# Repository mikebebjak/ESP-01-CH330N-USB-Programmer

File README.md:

# ESP-01-CH330N-USB-Programmer

This is a very simple but effective USB programmer for the ESP8266-01 Wifi microcontroller.
It uses a new CH330N SOIC-8 chip which is very easy to implement in ESP projects at a very low cost with few additional components.
The repository includes datasheet, drivers, schematics, Eagle board files and gerbers as well as an Eagle library file for the CH330N.
The drivers used for the CH330N are the same as the CH341.<br>

You can purchase the CH330N at: https://lcsc.com/product-detail/USB_CH330N_C108996.html<br>

You will need:<br>

1x CH330N USB transceiver<br>
1x AMS1117 TO-223 3.3V regulator<br>
1x Molex USB-A through-hole connector<br>
1x 8-pin 2mm socket for the ESP<br>
4x 10K 1206 resistors (for pullups and pulldowns)<br>
2x 0.1uF 1206 capacitors<br>
1x 6mm through-hole momentary push button for the reset button<br>
1x large electrolytic capacitor (220uF or higher at 6.3V min.)<br><br>
GPIO 0 is tied to GND permanently so this programmer cannot be used to boot the ESP (though it may sometimes work anyway).

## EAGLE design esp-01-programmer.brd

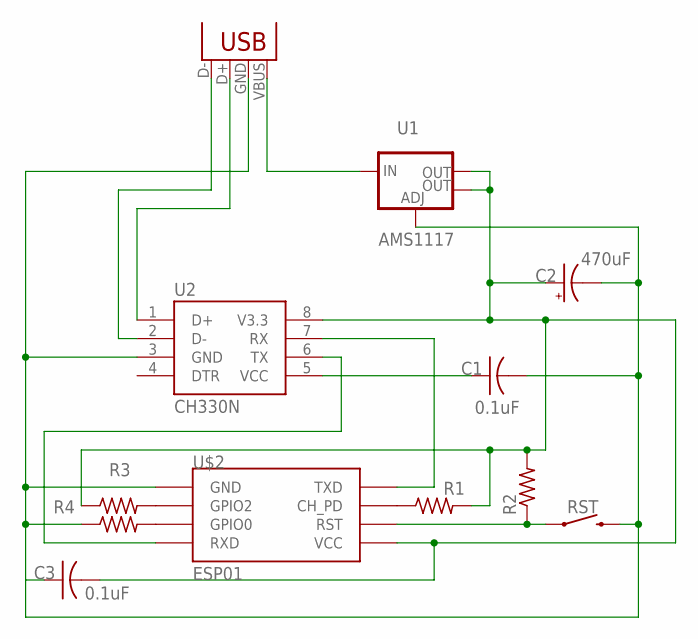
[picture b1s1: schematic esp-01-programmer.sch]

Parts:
C1, C3: 0.1uF; C1206
C2: 470uF; E2,5-6
R1, R2, R3, R4: R-US_R1206; R1206
RST: MOMENTARY-SWITCH-SPST-PTH-6.0MM; TACTILE_SWITCH_PTH_6.0MM
U1: AMS1117; SOT223
U2: CH330N; SOIC8
U$2: ESP01
USB-A: USB-A-H

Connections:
3.3V: C2.+, C3.2, R1.2, R2.2, R3.1, U1.2 (OUT), U1.4 (OUT), U2.8 (V3.3), U$2.VCC
D+: U2.1 (D+), USB-A.D+ (D-)
D-: U2.2 (D-), USB-A.D- (D+)
DTR: U2.4 (DTR)
GND: C1.2, C2.-, C3.1, R4.1, RST.3 (2), U1.1 (ADJ), U2.3 (GND), U$2.GND, USB-A.GND (VBUS)
unnamed: R2.1, RST.1, U$2.RST
unnamed: R4.2, U$2.GPIO0
unnamed: R3.2, U$2.GPIO2
unnamed: C1.1, U2.5 (VCC)
unnamed: U2.7 (RX), U$2.TX (TXD)
unnamed: U2.6 (TX), U$2.RX (RXD)
unnamed: R1.1, U$2.CH_PD
VUSB: U1.3 (IN), USB-A.VBUS (GND)

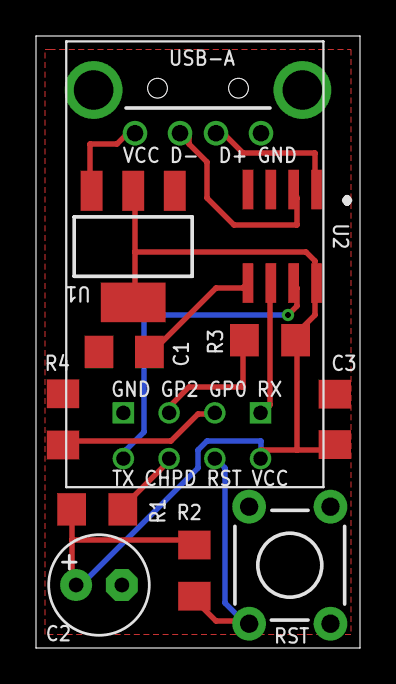
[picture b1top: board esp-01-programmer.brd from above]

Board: 2 copper layers, 18.0 x 34.0 mm, 12 parts (0 on the bottom side), 12 nets.

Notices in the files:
parts and their libraries:
SparkFun-Switches: Licensing: Creative Commons ShareAlike 4.0 International - https://creativecommons.org/licenses/by-sa/4.0
